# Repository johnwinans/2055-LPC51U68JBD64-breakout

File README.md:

# 2055-LPC51U68JBD64-breakout
LPC51U68JBD64 Breakout Board

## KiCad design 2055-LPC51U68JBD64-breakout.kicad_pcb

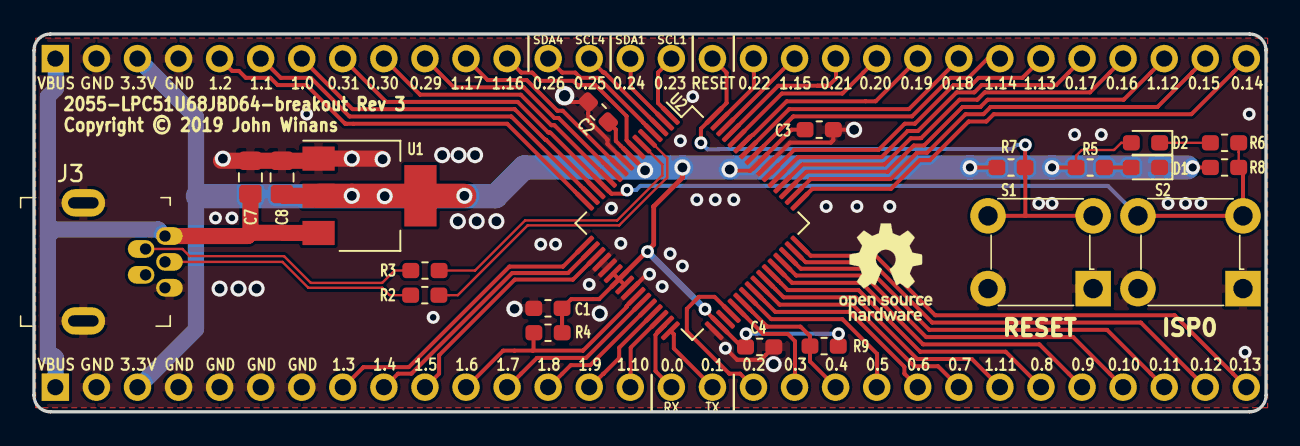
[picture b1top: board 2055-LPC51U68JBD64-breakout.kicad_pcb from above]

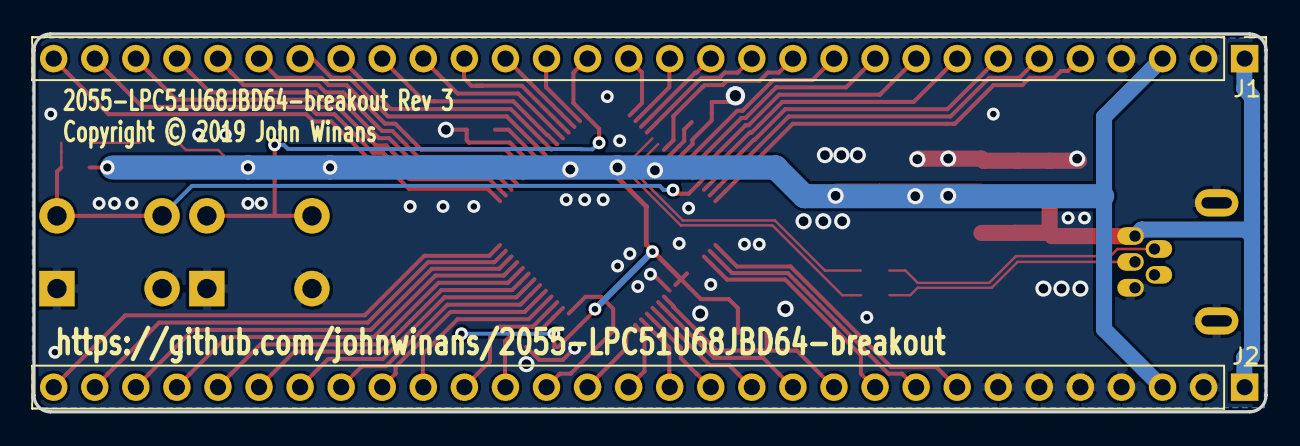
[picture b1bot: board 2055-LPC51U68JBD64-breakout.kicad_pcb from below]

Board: 2 copper layers, 76.2 x 23.4 mm, 24 parts (2 on the bottom side), 58 nets.

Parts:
C1, C2, C3, C4: .1uF; C_0603_1608Metric_Pad1.05x0.95mm_HandSolder
C7: 10uF; C_0805_2012Metric_Pad1.15x1.40mm_HandSolder
C8: 22uF; C_0805_2012Metric_Pad1.15x1.40mm_HandSolder
D1, D2: LED_ALT; LED_0603_1608Metric_Pad1.05x0.95mm_HandSolder
J1, J2: Conn_01x30; PinHeader_1x30_P2.54mm_Vertical
J3: 0548190519; USB_Mini_B_Female_548190519
LOGO1: Logo_Open_Hardware_Small; OSHW-Logo_5.7x6mm_SilkScreen
R2, R3: 33; R_0603_1608Metric_Pad1.05x0.95mm_HandSolder
R4, R7, R8, R9: 3K3; R_0603_1608Metric_Pad1.05x0.95mm_HandSolder
R5, R6: 330; R_0603_1608Metric_Pad1.05x0.95mm_HandSolder
S1, S2: 1825910-6; Switch_Tactile_THT_6x6mm
U1: AZ1117CH-3.3TRG1; SOT-223-3_TabPin2
U2: LPC51U68JBD64QL; TQFP-64_10x10mm_P0.5mm

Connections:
+3V3: C1.1, C2.1, C3.1, C4.1, C8.1, D2.2, J1.3, J2.3, R4.2, R5.2, R7.1, R8.1, R9.1, U1.2, U2.8, U2.22, U2.23, U2.24, U2.34, U2.56
/PIO0_0: J2.16, U2.31
/PIO0_1: J2.17, U2.32
/PIO0_2: J2.18, U2.36
/PIO0_3: J2.19, U2.37
/PIO0_4: J2.20, R9.2, U2.38
/PIO0_5: J2.21, U2.39
/PIO0_6: J2.22, U2.40
/PIO0_7: J2.23, U2.41
/PIO0_8: J2.25, U2.43
/PIO0_9: J2.26, U2.44
/PIO0_10: J2.27, U2.45
/PIO0_11: J2.28, U2.46
/PIO0_12: J2.29, U2.47
/PIO0_13: J2.30, U2.48
/PIO0_14: J1.30, U2.49
/PIO0_15: J1.29, U2.50
/PIO0_16: J1.27, U2.52
/PIO0_17: J1.26, U2.53
/PIO0_18: J1.23, U2.58
/PIO0_19: J1.22, U2.59
/PIO0_20: J1.21, U2.60
/PIO0_21: J1.20, U2.61
/PIO0_22: J1.18, U2.63
/PIO0_23: J1.16, U2.1
/PIO0_24: J1.15, U2.2
/PIO0_25: J1.14, U2.3
/PIO0_26: J1.13, U2.4
/PIO0_29: J1.10, U2.11
/PIO0_30: J1.9, U2.12
/PIO0_31: J1.8, R6.1, R8.2, S2.3, S2.4, U2.13
/PIO1_0: J1.7, U2.14
/PIO1_1: J1.6, U2.15
/PIO1_2: J1.5, U2.16
/PIO1_3: J2.8, U2.17
/PIO1_4: J2.9, U2.18
/PIO1_5: J2.10, U2.19
/PIO1_6: J2.11, R4.1, U2.26
/PIO1_7: J2.12, U2.27
/PIO1_8: J2.13, U2.28
/PIO1_9: J2.14, U2.29
/PIO1_10: J2.15, U2.30
/PIO1_11: J2.24, U2.42
/PIO1_12: J1.28, U2.51
/PIO1_13: J1.25, U2.54
/PIO1_14: J1.24, U2.57
/PIO1_15: J1.19, U2.62
/PIO1_16: J1.12, U2.7
/PIO1_17: J1.11, U2.10
/USB_DM: R3.2, U2.6
/USB_DP: R2.2, U2.5
/VBUS: C7.1, J1.1, J2.1, J3.5, U1.3
/~RESET~: J1.17, R7.2, S1.3, S1.4, U2.64
GND: C1.2, C2.2, C3.2, C4.2, C7.2, C8.2, D1.1, J1.2, J1.4, J2.2, J2.4, J2.5, J2.6, J2.7, J3.1, J3.SH, S1.1, S1.2, S2.1, S2.2, U1.1, U2.9, U2.20, U2.21, U2.25, U2.33, U2.55
unnamed: D1.2, R5.1
unnamed: D2.1, R6.2
unnamed: J3.3, R2.1
unnamed: J3.4, R3.1

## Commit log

2019-07-05 Initial import of Rev 2 forked from 2042.
2019-07-05 Update the copyright date
2019-07-08 Adjust edge cuts arc with wrong thickness.
2019-07-08 Fix rev number on front silkscreen
2019-07-08 Fix rev number on back silkscreen
2019-07-08 Added schematic pdf & open-source license files
2019-07-13 Reverse J3 pin order.
2019-07-27 Added gerbers for ordering from PCBWay.
2019-07-27 Correct thermal releif around C7 & C8.
2019-07-28 Clean up Digikey order numbers in the BOM.
2019-07-28 Update Rev number to 3a in the schematic title block.

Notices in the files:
2055-LPC51U68JBD64-breakout.kicad_pcb:
Copyright © 2019 John Winans
